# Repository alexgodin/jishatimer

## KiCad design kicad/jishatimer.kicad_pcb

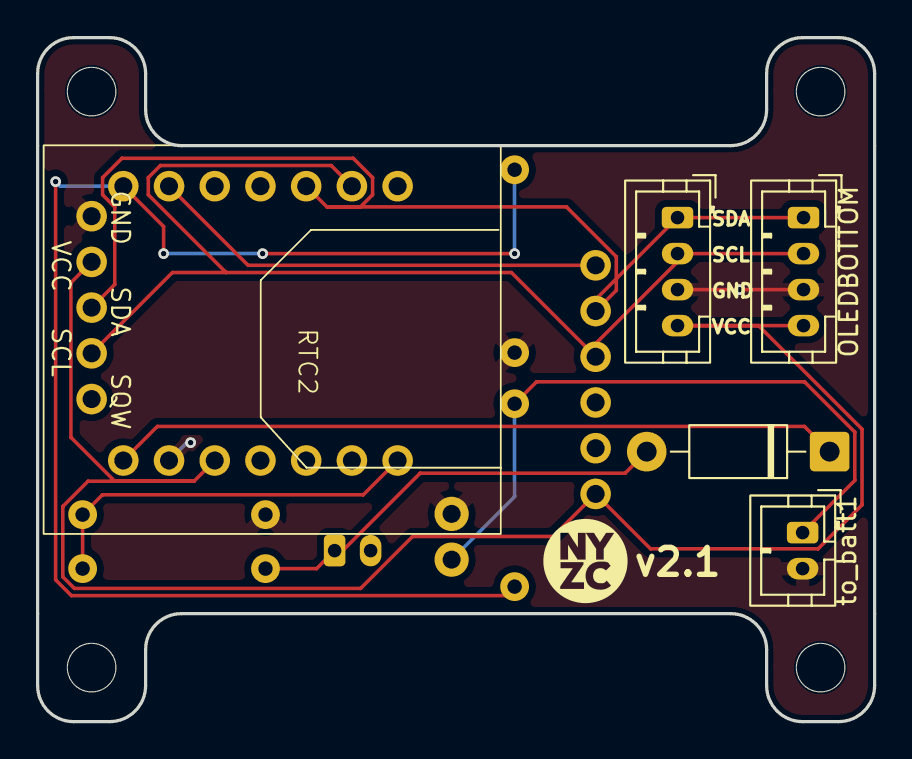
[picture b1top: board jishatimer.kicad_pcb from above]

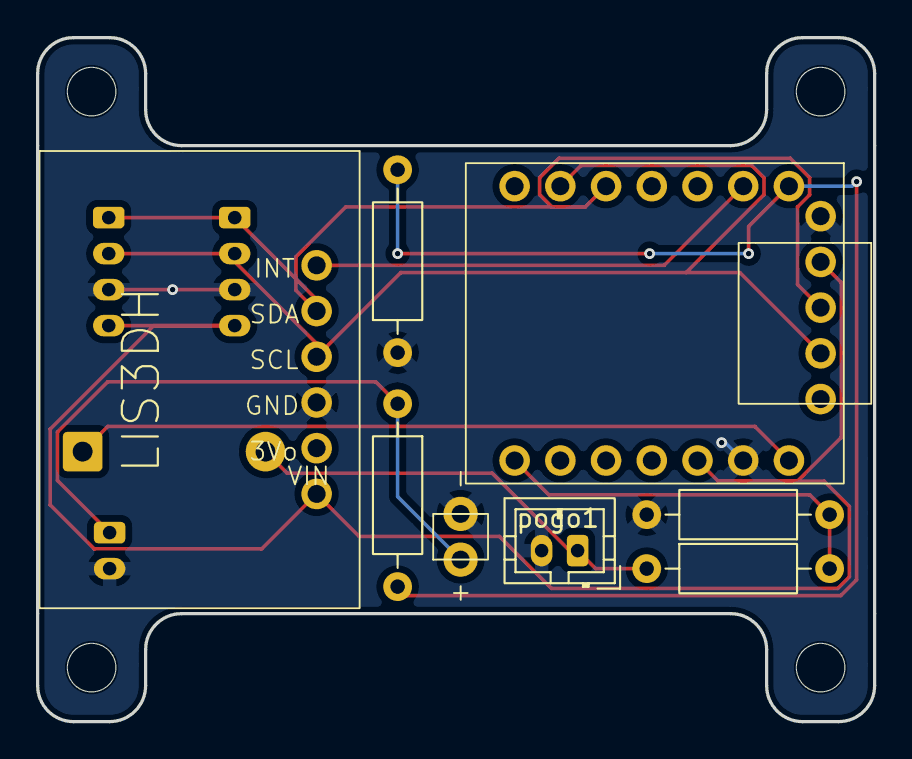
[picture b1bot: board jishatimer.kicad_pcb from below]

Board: 2 copper layers, 46.5 x 38.0 mm, 17 parts (8 on the bottom side), 10 nets.

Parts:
Accelerometer2: Adafruit_LIS3DH
Hole1, Hole1#2, Hole1#3, Hole2: MountingHole_2.7mm
OLEDBOTTOM1: JST_PH_B4B-PH-K_1x04_P2.00mm_Vertical
OLEDTOP1: JST_PH_B4B-PH-K_1x04_P2.00mm_Vertical
R1, R2, R3, R4: R; R_Axial_DIN0207_L6.3mm_D2.5mm_P10.16mm_Horizontal
RTC2: Adafruit_ PCF8523
Schottky1: D_Schottky; D_DO-41_SOD81_P10.16mm_Horizontal
XIAO1: Xiao_ESP32_C3
pogo1: JST_PH_B2B-PH-K_1x02_P2.00mm_Vertical
to_batt1: JST_PH_B2B-PH-K_1x02_P2.00mm_Vertical
to_xiao1: xiao_battery_connection

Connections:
+BATT: R2.1, to_batt1.1 (VCC), to_xiao1.+
GND: Accelerometer2.GND, OLEDBOTTOM1.3 (GND), OLEDTOP1.3 (GND), R1.1, R3.2, RTC2.GND, XIAO1.GND, pogo1.2 (GND), to_batt1.2 (GND), to_xiao1.-
unnamed: Accelerometer2.SCL, OLEDBOTTOM1.2 (SCL), OLEDTOP1.2 (SCL), RTC2.SCL, XIAO1.D5 (SCL)
unnamed: Accelerometer2.SDA, OLEDBOTTOM1.1 (SDA), OLEDTOP1.1 (SDA), RTC2.SDA, XIAO1.D4 (SDA)
unnamed: Accelerometer2.VIN, OLEDBOTTOM1.4 (VCC), OLEDTOP1.4 (VCC), RTC2.VCC, XIAO1.3V3 (3.3V)
unnamed: R3.1, R4.2, XIAO1.D7
unnamed: Schottky1.1 (K), XIAO1.5V (VUSB)
unnamed: R1.2, R2.2, XIAO1.D0 (A0)
unnamed: Accelerometer2.INT, XIAO1.D1 (A1)
VCC: R4.1, Schottky1.2 (A), pogo1.1 (+5v)

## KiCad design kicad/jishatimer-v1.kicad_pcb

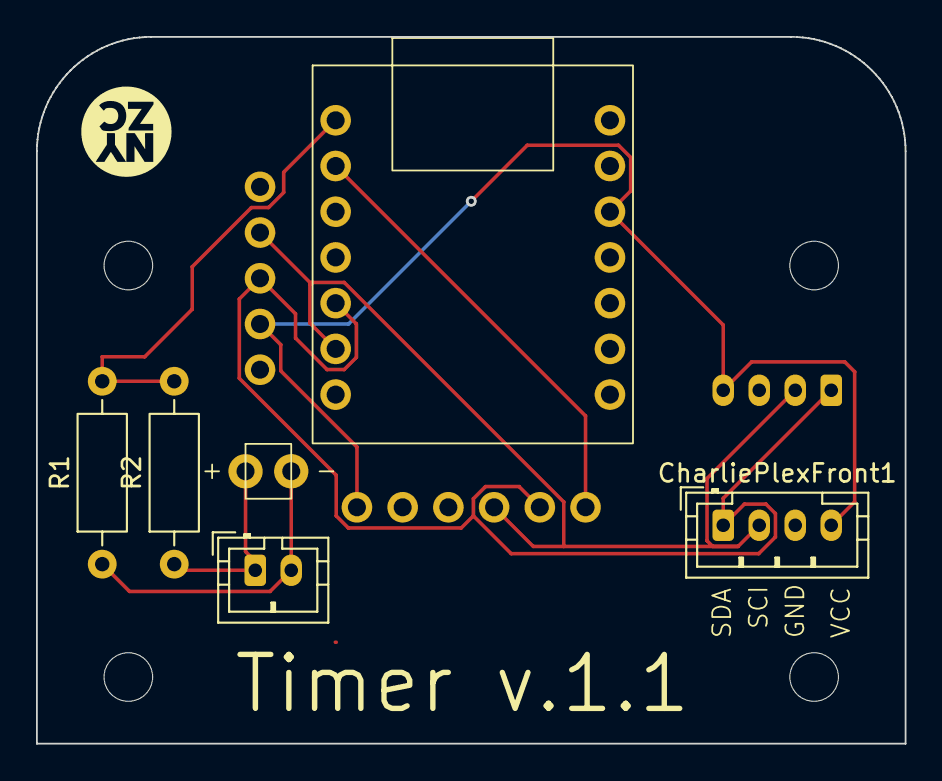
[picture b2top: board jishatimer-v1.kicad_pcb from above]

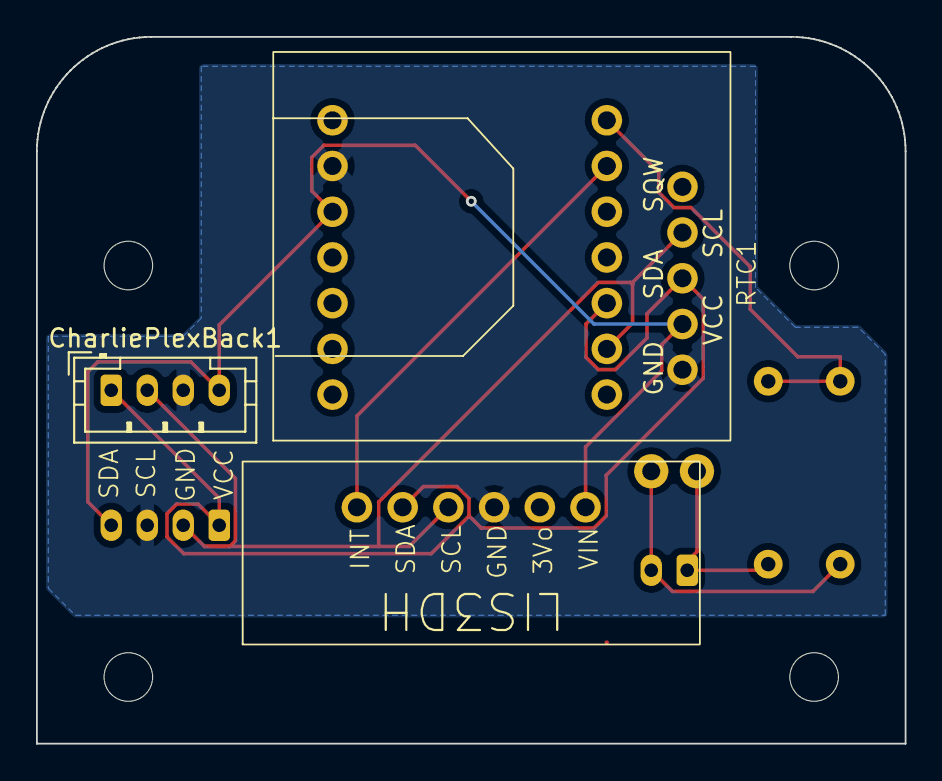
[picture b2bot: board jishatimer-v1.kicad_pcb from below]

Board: 2 copper layers, 48.3 x 39.3 mm, 9 parts (3 on the bottom side), 8 nets.

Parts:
Accelerometer1: Adafruit_LIS3DH
CharliePlexBack1: JST_PH_B4B-PH-K_1x04_P2.00mm_Vertical
CharliePlexFront1: JST_PH_B4B-PH-K_1x04_P2.00mm_Vertical
R1, R2: R; R_Axial_DIN0207_L6.3mm_D2.5mm_P10.16mm_Horizontal
RTC1: Adafruit_ PCF8523
XIAO1: Xiao_ESP32_C3
to_batt1: JST_PH_B2B-PH-K_1x02_P2.00mm_Vertical
to_xiao1: xiao_battery_connection

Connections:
unnamed: Accelerometer1.GND, CharliePlexBack1.3 (GND), CharliePlexFront1.3 (GND), RTC1.GND, XIAO1.GND
unnamed: Accelerometer1.VIN, CharliePlexBack1.4 (VCC), CharliePlexFront1.4 (VCC), RTC1.VCC, XIAO1.3V3 (3.3V)
unnamed: R1.2, R2.2, XIAO1.D0 (A0)
unnamed: Accelerometer1.INT, XIAO1.D1 (A1)
unnamed: Accelerometer1.SCL, CharliePlexBack1.2 (SCL), CharliePlexFront1.2 (SCL), RTC1.SCL, XIAO1.D5 (SCL)
unnamed: Accelerometer1.SDA, CharliePlexBack1.1 (SDA), CharliePlexFront1.1 (SDA), RTC1.SDA, XIAO1.D4 (SDA)
unnamed: R2.1, to_batt1.1 (+), to_xiao1.+
unnamed: R1.1, to_batt1.2 (-), to_xiao1.-

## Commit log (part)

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2025-12-18 old state
2026-01-23 without working clock
2026-03-02 cleaner
2026-03-16 with tests
